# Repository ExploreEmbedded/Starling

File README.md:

# Starling

Starling is live on CrowdSupply, back us and help this open-source project get to life :)

https://www.crowdsupply.com/explore-embedded/starling 

Starling, aims to be a modular Wifi connected hackable LED Display board. It can be used out of the box to display text messages and custom characters. It can be used from anywhere you're. It should also be able to expand and display messages from web; sports, schedules, social network notifications, whether data, news and anything else you want. The display should be able to expand without changes in the software. The display blocks can be added or removed on the fly 

For more details do visit the product wiki page.

http://exploreembedded.com/wiki/Starling:_A_simple_internet_connected_modular_led_display.

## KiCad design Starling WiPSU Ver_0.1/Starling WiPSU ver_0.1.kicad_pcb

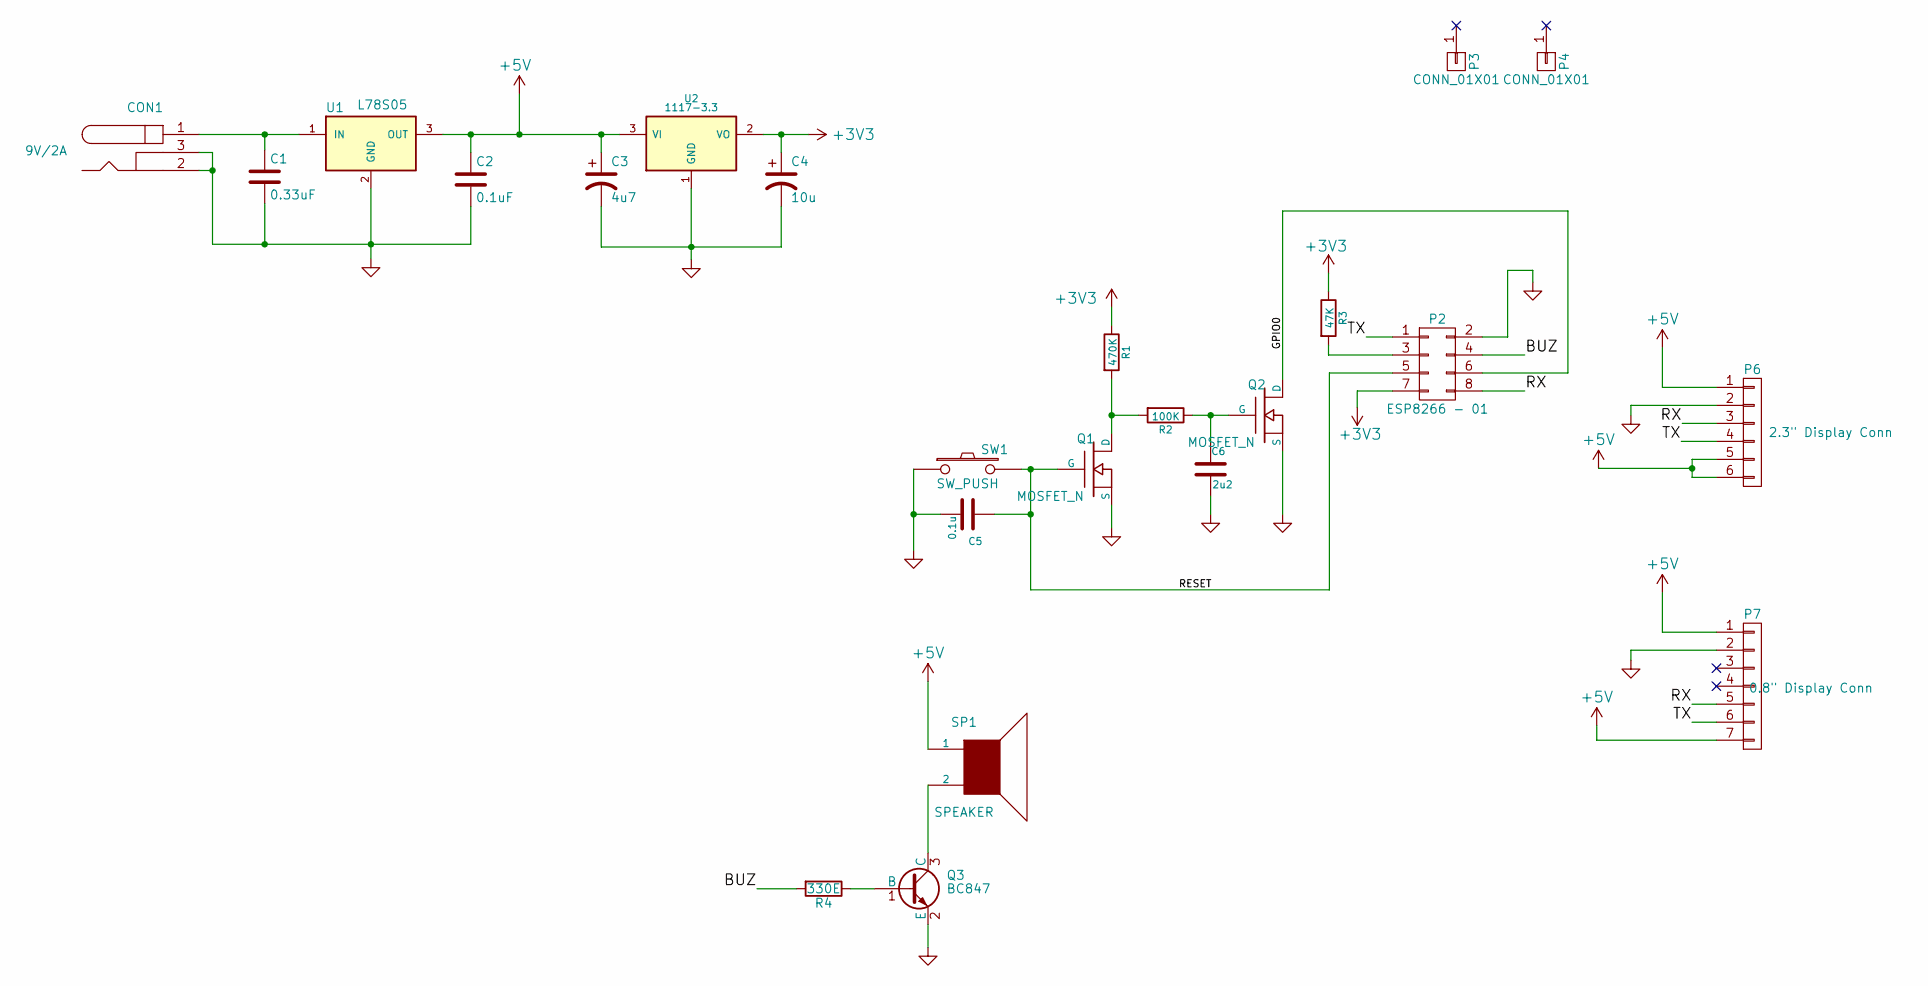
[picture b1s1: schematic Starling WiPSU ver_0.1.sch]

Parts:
C1: 0.33uF; C_0603
C2: 0.1uF; C_0603
C3: 4u7; TantalC_SizeA_EIA-3216_Wave
C4: 10u; TantalC_SizeA_EIA-3216_Wave
C5: 0.1u; C_0603
C6: 2u2; C_0603
CON1: 9V/2A; BARREL_JACK
P2: ESP8266 - 01; ESP-01
P3, P4: CONN_01X01; M3_mounting
P6: 2.3\" Display Conn; Pin_Header_Straight_1x06
P7: 0.8\" Display Conn; 1.27mm_smd_Header
Q1, Q2: MOSFET_N; sot23
Q3: BC847; SOT-23
R1: 470K; R_0603
R2: 100K; R_0603
R3: 47K; R_0603
R4: 330E; R_0603
SP1: SPEAKER; Buzzer_12x9.5RM7.6
SW1: SW_PUSH; smd_push
U1: L78S05; TO-220_Neutral123_Horizontal_MountedFromLS_LargePads
U2: 1117-3.3; SOT-223

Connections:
+3V3: C4.1, P2.7, R1.1, R3.1, U2.2 (VO)
+5V: C2.1, C3.1, P6.1, P6.5, P6.6, P7.1, P7.7, SP1.1, U1.3 (OUT), U2.3 (VI)
/BUZ: P2.4, R4.2
/GPIO0: P2.6, Q2.D
/RESET: C5.1, P2.5, Q1.G, SW1.2
/RX: P2.8, P6.3, P7.5
/TX: P2.1, P6.4, P7.6
GND: C1.2, C2.2, C3.2, C4.2, C5.2, C6.2, CON1.2, CON1.3, P2.2, P6.2, P7.2, Q1.S, Q2.S, Q3.2 (E), SW1.1, U1.2 (GND), U2.1 (GND)
unnamed: C1.1, CON1.1, U1.1 (IN)
unnamed: C6.1, Q2.G, R2.1
unnamed: P2.3, R3.2
unnamed: Q1.D, R1.2, R2.2
unnamed: Q3.1 (B), R4.1
unnamed: Q3.3 (C), SP1.2

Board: 2 copper layers, 25 parts (4 on the bottom side), 14 nets, no tracks yet.

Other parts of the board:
P1, P5: CONN_01X01; M3_mounting

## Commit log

2015-11-26 Updated hardware files kicad
2016-01-05 Wifi and PSU added
2016-01-30 Wifi and PSU ver0.1 updated
2016-01-30 Added Design Files
2016-01-30 added PCB and Code
2016-02-09 Sorted the structure
    Arranged all the files accordingly, do pull from here and maintain the
    structure
2016-02-29 Wifi BO added
